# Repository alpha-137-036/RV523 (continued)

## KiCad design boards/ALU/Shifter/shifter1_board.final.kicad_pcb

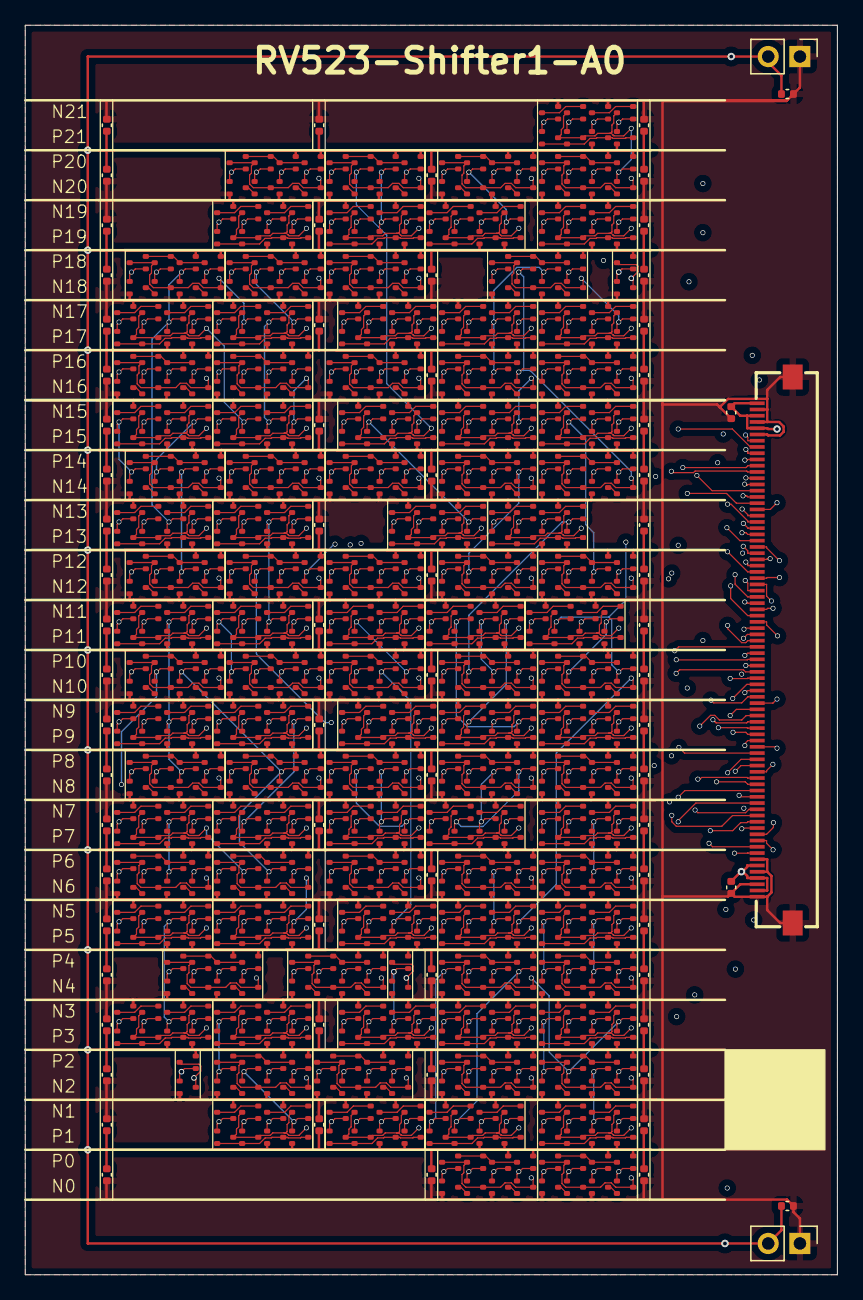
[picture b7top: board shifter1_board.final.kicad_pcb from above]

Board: 4 copper layers, 65.0 x 100.0 mm, 847 parts (0 on the bottom side), 426 nets.

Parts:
C1, C2, C3, C4: C_0402_1005Metric
j1: FPC-SMD_THD0518-80CL-GF
j2, j3: PinHeader_1x02_P2.54mm_Vertical
sh1._185_.N1, sh1._185_.N2, sh1._185_.N3, sh1._185_.N4, sh1._186_.N1, sh1._186_.N2, sh1._186_.N3, sh1._186_.N4, sh1._187_.N1, sh1._187_.N2, sh1._187_.N3, sh1._187_.N4, sh1._188_.N1, sh1._188_.N2, sh1._188_.N3, sh1._188_.N4, sh1._189_.N1, sh1._189_.N2, sh1._189_.N3, sh1._189_.N4, sh1._190_.N1, sh1._190_.N2, sh1._190_.N3, sh1._190_.N4, sh1._191_.N1, sh1._191_.N2, sh1._191_.N3, sh1._191_.N4, sh1._192_.N1, sh1._192_.N2, sh1._192_.N3, sh1._192_.N4, sh1._193_.N1, sh1._193_.N2, sh1._193_.N3, sh1._193_.N4, sh1._194_.N1, sh1._194_.N2, sh1._194_.N3, sh1._194_.N4, sh1._195_.N1, sh1._195_.N2, sh1._195_.N3, sh1._195_.N4, sh1._196_.N1, sh1._196_.N2, sh1._196_.N3, sh1._196_.N4, sh1._197_.N1, sh1._197_.N2, sh1._197_.N3, sh1._197_.N4, sh1._198_.N1, sh1._198_.N2, sh1._198_.N3, sh1._198_.N4, sh1._199_.N1, sh1._199_.N2, sh1._199_.N3, sh1._199_.N4, sh1._200_.N1, sh1._200_.N2, sh1._200_.N3, sh1._200_.N4, sh1._201_.N1, sh1._201_.N2, sh1._201_.N3, sh1._201_.N4, sh1._202_.N1, sh1._202_.N2, sh1._202_.N3, sh1._202_.N4, sh1._203_.N1, sh1._203_.N2, sh1._203_.N3, sh1._203_.N4, sh1._204_.N1, sh1._204_.N2, sh1._204_.N3, sh1._204_.N4, sh1._205_.N1, sh1._205_.N2, sh1._205_.N3, sh1._205_.N4, sh1._206_.N1, sh1._206_.N2, sh1._206_.N3, sh1._206_.N4, sh1._207_.N1, sh1._207_.N2, sh1._207_.N3, sh1._207_.N4, sh1._208_.N1, sh1._208_.N2, sh1._208_.N3, sh1._208_.N4, sh1._209_.N1, sh1._209_.N2, sh1._209_.N3, sh1._209_.N4, sh1._210_.N1, sh1._210_.N2, sh1._210_.N3, sh1._210_.N4, sh1._211_.N1, sh1._211_.N2, sh1._211_.N3, sh1._211_.N4, sh1._212_.N1, sh1._212_.N2, sh1._212_.N3, sh1._212_.N4, sh1._213_.N1, sh1._213_.N2, sh1._213_.N3, sh1._213_.N4, sh1._214_.N1, sh1._214_.N2, sh1._214_.N3, sh1._214_.N4, sh1._215_.N1, sh1._215_.N2, sh1._215_.N3, sh1._215_.N4, sh1._216_.N1, sh1._216_.N2, sh1._216_.N3, sh1._216_.N4, sh1._217_.N1, sh1._218_.N1, sh1._219_.N1, sh1._220_.N1, sh1._220_.N2, sh1._220_.N3, sh1._220_.N4, sh1._221_.N1, sh1._221_.N2, sh1._221_.N3, sh1._221_.N4, sh1._222_.N1, sh1._222_.N2, sh1._222_.N3, sh1._222_.N4, sh1._223_.N1, sh1._223_.N2, sh1._223_.N3, sh1._223_.N4, sh1._224_.N1, sh1._224_.N2, sh1._224_.N3, sh1._224_.N4, sh1._225_.N1, sh1._225_.N2, sh1._225_.N3, sh1._225_.N4, sh1._226_.N1, sh1._226_.N2, sh1._226_.N3, sh1._226_.N4, sh1._227_.N1, sh1._227_.N2, sh1._227_.N3, sh1._227_.N4, sh1._228_.N1, sh1._228_.N2, sh1._228_.N3, sh1._228_.N4, sh1._229_.N1, sh1._229_.N2, sh1._229_.N3, sh1._229_.N4, sh1._230_.N1, sh1._230_.N2, sh1._230_.N3, sh1._230_.N4, sh1._231_.N1, sh1._231_.N2, sh1._231_.N3, sh1._231_.N4, sh1._232_.N1, sh1._232_.N2, sh1._232_.N3, sh1._232_.N4, sh1._233_.N1, sh1._233_.N2, sh1._233_.N3, sh1._233_.N4, sh1._234_.N1, sh1._234_.N2, sh1._234_.N3, sh1._234_.N4, sh1._235_.N1, sh1._235_.N2, sh1._235_.N3, sh1._235_.N4, sh1._236_.N1, sh1._236_.N2, sh1._236_.N3, sh1._236_.N4, sh1._237_.N1, sh1._237_.N2, sh1._237_.N3, sh1._237_.N4, sh1._238_.N1, sh1._238_.N2, sh1._238_.N3, sh1._238_.N4, sh1._239_.N1, sh1._239_.N2, sh1._239_.N3, sh1._239_.N4, sh1._240_.N1, sh1._240_.N2, sh1._240_.N3, sh1._240_.N4, sh1._241_.N1, sh1._241_.N2, sh1._241_.N3, sh1._241_.N4, sh1._242_.N1, sh1._242_.N2, sh1._242_.N3, sh1._242_.N4, sh1._243_.N1, sh1._243_.N2, sh1._243_.N3, sh1._243_.N4, sh1._244_.N1, sh1._244_.N2, sh1._244_.N3, sh1._244_.N4, sh1._245_.N1, sh1._245_.N2, sh1._245_.N3, sh1._245_.N4, sh1._246_.N1, sh1._246_.N2, sh1._246_.N3, sh1._246_.N4, sh1._247_.N1, sh1._247_.N2, sh1._247_.N3, sh1._247_.N4, sh1._248_.N1, sh1._248_.N2, sh1._248_.N3, sh1._248_.N4, sh1._249_.N1, sh1._249_.N2, sh1._249_.N3, sh1._249_.N4, sh1._250_.N1, sh1._250_.N2, sh1._250_.N3, sh1._250_.N4, sh1._251_.N1, sh1._251_.N2, sh1._251_.N3, sh1._251_.N4, sh1._252_.N1, sh1._252_.N2, sh1._252_.N3, sh1._252_.N4, sh1._253_.N1, sh1._253_.N2, sh1._253_.N3, sh1._253_.N4, sh1._254_.N1, sh1._254_.N2, sh1._254_.N3, sh1._254_.N4, sh1._255_.N1, sh1._255_.N2, sh1._255_.N3, sh1._255_.N4, sh1._256_.N1, sh1._256_.N2, sh1._256_.N3, sh1._256_.N4, sh1._257_.N1, sh1._257_.N2, sh1._257_.N3, sh1._257_.N4, sh1._258_.N1, sh1._258_.N2, sh1._258_.N3, sh1._258_.N4, sh1._259_.N1, sh1._259_.N2, sh1._259_.N3, sh1._259_.N4, sh1._260_.N1, sh1._260_.N2, sh1._260_.N3, sh1._260_.N4, sh1._261_.N1, sh1._261_.N2, sh1._261_.N3, sh1._261_.N4, sh1._262_.N1, sh1._262_.N2, sh1._262_.N3, sh1._262_.N4, sh1._263_.N1, sh1._263_.N2, sh1._263_.N3, sh1._263_.N4, sh1._264_.N1, sh1._264_.N2, sh1._264_.N3, sh1._264_.N4, sh1._265_.N1, sh1._265_.N2, sh1._265_.N3, sh1._265_.N4, sh1._266_.N1, sh1._266_.N2, sh1._266_.N3, sh1._266_.N4, sh1._267_.N1, sh1._267_.N2, sh1._267_.N3, sh1._267_.N4, sh1._268_.N1, sh1._268_.N2, sh1._268_.N3, sh1._268_.N4, sh1._269_.N1, sh1._269_.N2, sh1._269_.N3, sh1._269_.N4, sh1._270_.N1, sh1._270_.N2, sh1._270_.N3, sh1._270_.N4, sh1._271_.N1, sh1._271_.N2, sh1._271_.N3, sh1._271_.N4, sh1._272_.N1, sh1._272_.N2, sh1._272_.N3, sh1._272_.N4, sh1._273_.N1, sh1._273_.N2, sh1._273_.N3, sh1._273_.N4, sh1._274_.N1, sh1._274_.N2, sh1._274_.N3, sh1._274_.N4, sh1._275_.N1, sh1._275_.N2, sh1._275_.N3, sh1._275_.N4, sh1._276_.N1, sh1._276_.N2, sh1._276_.N3, sh1._276_.N4, sh1._277_.N1, sh1._277_.N2, sh1._277_.N3, sh1._277_.N4, sh1._278_.N1, sh1._278_.N2, sh1._278_.N3, sh1._278_.N4, sh1._279_.N1, sh1._279_.N2, sh1._279_.N3, sh1._279_.N4, sh1._280_.N1, sh1._280_.N2, sh1._280_.N3, sh1._280_.N4, sh1._281_.N1, sh1._281_.N2, sh1._281_.N3, sh1._281_.N4, sh1._282_.N1, sh1._282_.N2, sh1._282_.N3, sh1._282_.N4, sh1._283_.N1, sh1._283_.N2, sh1._283_.N3, sh1._283_.N4: NMOS; SOT523
sh1._185_.P1, sh1._185_.P2, sh1._185_.P3, sh1._185_.P4, sh1._186_.P1, sh1._186_.P2, sh1._186_.P3, sh1._186_.P4, sh1._187_.P1, sh1._187_.P2, sh1._187_.P3, sh1._187_.P4, sh1._188_.P1, sh1._188_.P2, sh1._188_.P3, sh1._188_.P4, sh1._189_.P1, sh1._189_.P2, sh1._189_.P3, sh1._189_.P4, sh1._190_.P1, sh1._190_.P2, sh1._190_.P3, sh1._190_.P4, sh1._191_.P1, sh1._191_.P2, sh1._191_.P3, sh1._191_.P4, sh1._192_.P1, sh1._192_.P2, sh1._192_.P3, sh1._192_.P4, sh1._193_.P1, sh1._193_.P2, sh1._193_.P3, sh1._193_.P4, sh1._194_.P1, sh1._194_.P2, sh1._194_.P3, sh1._194_.P4, sh1._195_.P1, sh1._195_.P2, sh1._195_.P3, sh1._195_.P4, sh1._196_.P1, sh1._196_.P2, sh1._196_.P3, sh1._196_.P4, sh1._197_.P1, sh1._197_.P2, sh1._197_.P3, sh1._197_.P4, sh1._198_.P1, sh1._198_.P2, sh1._198_.P3, sh1._198_.P4, sh1._199_.P1, sh1._199_.P2, sh1._199_.P3, sh1._199_.P4, sh1._200_.P1, sh1._200_.P2, sh1._200_.P3, sh1._200_.P4, sh1._201_.P1, sh1._201_.P2, sh1._201_.P3, sh1._201_.P4, sh1._202_.P1, sh1._202_.P2, sh1._202_.P3, sh1._202_.P4, sh1._203_.P1, sh1._203_.P2, sh1._203_.P3, sh1._203_.P4, sh1._204_.P1, sh1._204_.P2, sh1._204_.P3, sh1._204_.P4, sh1._205_.P1, sh1._205_.P2, sh1._205_.P3, sh1._205_.P4, sh1._206_.P1, sh1._206_.P2, sh1._206_.P3, sh1._206_.P4, sh1._207_.P1, sh1._207_.P2, sh1._207_.P3, sh1._207_.P4, sh1._208_.P1, sh1._208_.P2, sh1._208_.P3, sh1._208_.P4, sh1._209_.P1, sh1._209_.P2, sh1._209_.P3, sh1._209_.P4, sh1._210_.P1, sh1._210_.P2, sh1._210_.P3, sh1._210_.P4, sh1._211_.P1, sh1._211_.P2, sh1._211_.P3, sh1._211_.P4, sh1._212_.P1, sh1._212_.P2, sh1._212_.P3, sh1._212_.P4, sh1._213_.P1, sh1._213_.P2, sh1._213_.P3, sh1._213_.P4, sh1._214_.P1, sh1._214_.P2, sh1._214_.P3, sh1._214_.P4, sh1._215_.P1, sh1._215_.P2, sh1._215_.P3, sh1._215_.P4, sh1._216_.P1, sh1._216_.P2, sh1._216_.P3, sh1._216_.P4, sh1._217_.P1, sh1._218_.P1, sh1._219_.P1, sh1._220_.P1, sh1._220_.P2, sh1._220_.P3, sh1._220_.P4, sh1._221_.P1, sh1._221_.P2, sh1._221_.P3, sh1._221_.P4, sh1._222_.P1, sh1._222_.P2, sh1._222_.P3, sh1._222_.P4, sh1._223_.P1, sh1._223_.P2, sh1._223_.P3, sh1._223_.P4, sh1._224_.P1, sh1._224_.P2, sh1._224_.P3, sh1._224_.P4, sh1._225_.P1, sh1._225_.P2, sh1._225_.P3, sh1._225_.P4, sh1._226_.P1, sh1._226_.P2, sh1._226_.P3, sh1._226_.P4, sh1._227_.P1, sh1._227_.P2, sh1._227_.P3, sh1._227_.P4, sh1._228_.P1, sh1._228_.P2, sh1._228_.P3, sh1._228_.P4, sh1._229_.P1, sh1._229_.P2, sh1._229_.P3, sh1._229_.P4, sh1._230_.P1, sh1._230_.P2, sh1._230_.P3, sh1._230_.P4, sh1._231_.P1, sh1._231_.P2, sh1._231_.P3, sh1._231_.P4, sh1._232_.P1, sh1._232_.P2, sh1._232_.P3, sh1._232_.P4, sh1._233_.P1, sh1._233_.P2, sh1._233_.P3, sh1._233_.P4, sh1._234_.P1, sh1._234_.P2, sh1._234_.P3, sh1._234_.P4, sh1._235_.P1, sh1._235_.P2, sh1._235_.P3, sh1._235_.P4, sh1._236_.P1, sh1._236_.P2, sh1._236_.P3, sh1._236_.P4, sh1._237_.P1, sh1._237_.P2, sh1._237_.P3, sh1._237_.P4, sh1._238_.P1, sh1._238_.P2, sh1._238_.P3, sh1._238_.P4, sh1._239_.P1, sh1._239_.P2, sh1._239_.P3, sh1._239_.P4, sh1._240_.P1, sh1._240_.P2, sh1._240_.P3, sh1._240_.P4, sh1._241_.P1, sh1._241_.P2, sh1._241_.P3, sh1._241_.P4, sh1._242_.P1, sh1._242_.P2, sh1._242_.P3, sh1._242_.P4, sh1._243_.P1, sh1._243_.P2, sh1._243_.P3, sh1._243_.P4, sh1._244_.P1, sh1._244_.P2, sh1._244_.P3, sh1._244_.P4, sh1._245_.P1, sh1._245_.P2, sh1._245_.P3, sh1._245_.P4, sh1._246_.P1, sh1._246_.P2, sh1._246_.P3, sh1._246_.P4, sh1._247_.P1, sh1._247_.P2, sh1._247_.P3, sh1._247_.P4, sh1._248_.P1, sh1._248_.P2, sh1._248_.P3, sh1._248_.P4, sh1._249_.P1, sh1._249_.P2, sh1._249_.P3, sh1._249_.P4, sh1._250_.P1, sh1._250_.P2, sh1._250_.P3, sh1._250_.P4, sh1._251_.P1, sh1._251_.P2, sh1._251_.P3, sh1._251_.P4, sh1._252_.P1, sh1._252_.P2, sh1._252_.P3, sh1._252_.P4, sh1._253_.P1, sh1._253_.P2, sh1._253_.P3, sh1._253_.P4, sh1._254_.P1, sh1._254_.P2, sh1._254_.P3, sh1._254_.P4, sh1._255_.P1, sh1._255_.P2, sh1._255_.P3, sh1._255_.P4, sh1._256_.P1, sh1._256_.P2, sh1._256_.P3, sh1._256_.P4, sh1._257_.P1, sh1._257_.P2, sh1._257_.P3, sh1._257_.P4, sh1._258_.P1, sh1._258_.P2, sh1._258_.P3, sh1._258_.P4, sh1._259_.P1, sh1._259_.P2, sh1._259_.P3, sh1._259_.P4, sh1._260_.P1, sh1._260_.P2, sh1._260_.P3, sh1._260_.P4, sh1._261_.P1, sh1._261_.P2, sh1._261_.P3, sh1._261_.P4, sh1._262_.P1, sh1._262_.P2, sh1._262_.P3, sh1._262_.P4, sh1._263_.P1, sh1._263_.P2, sh1._263_.P3, sh1._263_.P4, sh1._264_.P1, sh1._264_.P2, sh1._264_.P3, sh1._264_.P4, sh1._265_.P1, sh1._265_.P2, sh1._265_.P3, sh1._265_.P4, sh1._266_.P1, sh1._266_.P2, sh1._266_.P3, sh1._266_.P4, sh1._267_.P1, sh1._267_.P2, sh1._267_.P3, sh1._267_.P4, sh1._268_.P1, sh1._268_.P2, sh1._268_.P3, sh1._268_.P4, sh1._269_.P1, sh1._269_.P2, sh1._269_.P3, sh1._269_.P4, sh1._270_.P1, sh1._270_.P2, sh1._270_.P3, sh1._270_.P4, sh1._271_.P1, sh1._271_.P2, sh1._271_.P3, sh1._271_.P4, sh1._272_.P1, sh1._272_.P2, sh1._272_.P3, sh1._272_.P4, sh1._273_.P1, sh1._273_.P2, sh1._273_.P3, sh1._273_.P4, sh1._274_.P1, sh1._274_.P2, sh1._274_.P3, sh1._274_.P4, sh1._275_.P1, sh1._275_.P2, sh1._275_.P3, sh1._275_.P4, sh1._276_.P1, sh1._276_.P2, sh1._276_.P3, sh1._276_.P4, sh1._277_.P1, sh1._277_.P2, sh1._277_.P3, sh1._277_.P4, sh1._278_.P1, sh1._278_.P2, sh1._278_.P3, sh1._278_.P4, sh1._279_.P1, sh1._279_.P2, sh1._279_.P3, sh1._279_.P4, sh1._280_.P1, sh1._280_.P2, sh1._280_.P3, sh1._280_.P4, sh1._281_.P1, sh1._281_.P2, sh1._281_.P3, sh1._281_.P4, sh1._282_.P1, sh1._282_.P2, sh1._282_.P3, sh1._282_.P4, sh1._283_.P1, sh1._283_.P2, sh1._283_.P3, sh1._283_.P4: PMOS; SOT523
sh1.decap0_L.C, sh1.decap0_M.C, sh1.decap0_R.C, sh1.decap1_L.C, sh1.decap1_M.C, sh1.decap1_R.C, sh1.decap2_L.C, sh1.decap2_M.C, sh1.decap2_R.C, sh1.decap3_L.C, sh1.decap3_M.C, sh1.decap3_R.C, sh1.decap4_L.C, sh1.decap4_M.C, sh1.decap4_R.C, sh1.decap5_L.C, sh1.decap5_M.C, sh1.decap5_R.C, sh1.decap6_L.C, sh1.decap6_M.C, sh1.decap6_R.C, sh1.decap7_L.C, sh1.decap7_M.C, sh1.decap7_R.C, sh1.decap8_L.C, sh1.decap8_M.C, sh1.decap8_R.C, sh1.decap9_L.C, sh1.decap9_M.C, sh1.decap9_R.C, sh1.decap10_L.C, sh1.decap10_M.C, sh1.decap10_R.C, sh1.decap11_L.C, sh1.decap11_M.C, sh1.decap11_R.C, sh1.decap12_L.C, sh1.decap12_M.C, sh1.decap12_R.C, sh1.decap13_L.C, sh1.decap13_M.C, sh1.decap13_R.C, sh1.decap14_L.C, sh1.decap14_M.C, sh1.decap14_R.C, sh1.decap15_L.C, sh1.decap15_M.C, sh1.decap15_R.C, sh1.decap16_L.C, sh1.decap16_M.C, sh1.decap16_R.C, sh1.decap17_L.C, sh1.decap17_M.C, sh1.decap17_R.C, sh1.decap18_L.C, sh1.decap18_M.C, sh1.decap18_R.C, sh1.decap19_L.C, sh1.decap19_M.C, sh1.decap19_R.C, sh1.decap20_L.C, sh1.decap20_M.C, sh1.decap20_R.C, sh1.decap21_L.C, sh1.decap21_M.C, sh1.decap21_R.C: 0.1u; C_0402_1005Metric

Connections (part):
A0: j1.74 (pins.74), sh1._219_.N1.1 (G), sh1._219_.P1.1 (G), sh1._252_.N4.1 (G), sh1._252_.P4.1 (G), sh1._263_.N4.1 (G), sh1._263_.P4.1 (G)
A.0: j1.71 (pins.71), sh1._193_.N3.1 (G), sh1._193_.P3.1 (G), sh1._200_.N2.1 (G), sh1._200_.P2.1 (G)
A.1: j1.69 (pins.69), sh1._192_.N4.1 (G), sh1._192_.P4.1 (G), sh1._211_.N2.1 (G), sh1._211_.P2.1 (G)
A.2: j1.67 (pins.67), sh1._190_.N2.1 (G), sh1._190_.P2.1 (G), sh1._191_.N4.1 (G), sh1._191_.P4.1 (G)
A.3: j1.65 (pins.65), sh1._189_.N4.1 (G), sh1._189_.P4.1 (G), sh1._194_.N2.1 (G), sh1._194_.P2.1 (G)
A.4: j1.63 (pins.63), sh1._188_.N4.1 (G), sh1._188_.P4.1 (G), sh1._195_.N2.1 (G), sh1._195_.P2.1 (G)
A.5: j1.61 (pins.61), sh1._187_.N4.1 (G), sh1._187_.P4.1 (G), sh1._196_.N2.1 (G), sh1._196_.P2.1 (G)
A.6: j1.59 (pins.59), sh1._186_.N4.1 (G), sh1._186_.P4.1 (G), sh1._197_.N2.1 (G), sh1._197_.P2.1 (G)
A.7: j1.57 (pins.57), sh1._185_.N4.1 (G), sh1._185_.P4.1 (G), sh1._198_.N2.1 (G), sh1._198_.P2.1 (G)
A.8: j1.55 (pins.55), sh1._199_.N2.1 (G), sh1._199_.P2.1 (G), sh1._216_.N4.1 (G), sh1._216_.P4.1 (G)
A.9: j1.53 (pins.53), sh1._201_.N2.1 (G), sh1._201_.P2.1 (G), sh1._215_.N4.1 (G), sh1._215_.P4.1 (G)
A.10: j1.51 (pins.51), sh1._202_.N2.1 (G), sh1._202_.P2.1 (G), sh1._214_.N4.1 (G), sh1._214_.P4.1 (G)
A.11: j1.49 (pins.49), sh1._203_.N2.1 (G), sh1._203_.P2.1 (G), sh1._213_.N4.1 (G), sh1._213_.P4.1 (G)
A.12: j1.47 (pins.47), sh1._204_.N2.1 (G), sh1._204_.P2.1 (G), sh1._212_.N4.1 (G), sh1._212_.P4.1 (G)
A.13: j1.45 (pins.45), sh1._205_.N2.1 (G), sh1._205_.P2.1 (G), sh1._210_.N4.1 (G), sh1._210_.P4.1 (G)
A.14: j1.43 (pins.43), sh1._206_.N2.1 (G), sh1._206_.P2.1 (G), sh1._209_.N4.1 (G), sh1._209_.P4.1 (G)
A.15: j1.41 (pins.41), sh1._207_.N2.1 (G), sh1._207_.P2.1 (G), sh1._208_.N4.1 (G), sh1._208_.P4.1 (G)
A.16: j1.39 (pins.39), sh1._207_.N4.1 (G), sh1._207_.P4.1 (G), sh1._208_.N2.1 (G), sh1._208_.P2.1 (G)
A.17: j1.37 (pins.37), sh1._206_.N4.1 (G), sh1._206_.P4.1 (G), sh1._209_.N2.1 (G), sh1._209_.P2.1 (G)
A.18: j1.35 (pins.35), sh1._205_.N4.1 (G), sh1._205_.P4.1 (G), sh1._210_.N2.1 (G), sh1._210_.P2.1 (G)
A.19: j1.33 (pins.33), sh1._204_.N4.1 (G), sh1._204_.P4.1 (G), sh1._212_.N2.1 (G), sh1._212_.P2.1 (G)
A.20: j1.31 (pins.31), sh1._203_.N4.1 (G), sh1._203_.P4.1 (G), sh1._213_.N2.1 (G), sh1._213_.P2.1 (G)
A.21: j1.29 (pins.29), sh1._202_.N4.1 (G), sh1._202_.P4.1 (G), sh1._214_.N2.1 (G), sh1._214_.P2.1 (G)
A.22: j1.27 (pins.27), sh1._201_.N4.1 (G), sh1._201_.P4.1 (G), sh1._215_.N2.1 (G), sh1._215_.P2.1 (G)
A.23: j1.25 (pins.25), sh1._199_.N4.1 (G), sh1._199_.P4.1 (G), sh1._216_.N2.1 (G), sh1._216_.P2.1 (G)
A.24: j1.23 (pins.23), sh1._185_.N2.1 (G), sh1._185_.P2.1 (G), sh1._198_.N4.1 (G), sh1._198_.P4.1 (G)
A.25: j1.21 (pins.21), sh1._186_.N2.1 (G), sh1._186_.P2.1 (G), sh1._197_.N4.1 (G), sh1._197_.P4.1 (G)
A.26: j1.19 (pins.19), sh1._187_.N2.1 (G), sh1._187_.P2.1 (G), sh1._196_.N4.1 (G), sh1._196_.P4.1 (G)
A.27: j1.17 (pins.17), sh1._188_.N2.1 (G), sh1._188_.P2.1 (G), sh1._195_.N4.1 (G), sh1._195_.P4.1 (G)
A.28: j1.15 (pins.15), sh1._189_.N2.1 (G), sh1._189_.P2.1 (G), sh1._194_.N4.1 (G), sh1._194_.P4.1 (G)
A.29: j1.13 (pins.13), sh1._190_.N4.1 (G), sh1._190_.P4.1 (G), sh1._191_.N2.1 (G), sh1._191_.P2.1 (G)
A.30: j1.11 (pins.11), sh1._192_.N2.1 (G), sh1._192_.P2.1 (G), sh1._211_.N4.1 (G), sh1._211_.P4.1 (G)
A.31: j1.9 (pins.9), sh1._193_.N2.1 (G), sh1._193_.P2.1 (G), sh1._200_.N4.1 (G), sh1._200_.P4.1 (G)
B.0: sh1._217_.N1.1 (G), sh1._217_.P1.1 (G), sh1._220_.N3.1 (G), sh1._220_.P3.1 (G), sh1._221_.N3.1 (G), sh1._221_.P3.1 (G), sh1._222_.N3.1 (G), sh1._222_.P3.1 (G), sh1._223_.N3.1 (G), sh1._223_.P3.1 (G), sh1._224_.N3.1 (G), sh1._224_.P3.1 (G), sh1._225_.N3.1 (G), sh1._225_.P3.1 (G), sh1._226_.N3.1 (G), sh1._226_.P3.1 (G), sh1._227_.N3.1 (G), sh1._227_.P3.1 (G), sh1._228_.N3.1 (G), sh1._228_.P3.1 (G), sh1._229_.N3.1 (G), sh1._229_.P3.1 (G), sh1._230_.N3.1 (G), sh1._230_.P3.1 (G), sh1._231_.N3.1 (G), sh1._231_.P3.1 (G), sh1._232_.N3.1 (G), sh1._232_.P3.1 (G), sh1._233_.N3.1 (G), sh1._233_.P3.1 (G), sh1._234_.N3.1 (G), sh1._234_.P3.1 (G), sh1._235_.N3.1 (G), sh1._235_.P3.1 (G), sh1._236_.N3.1 (G), sh1._236_.P3.1 (G), sh1._237_.N3.1 (G), sh1._237_.P3.1 (G), sh1._238_.N3.1 (G), sh1._238_.P3.1 (G), sh1._239_.N3.1 (G), sh1._239_.P3.1 (G), sh1._240_.N3.1 (G), sh1._240_.P3.1 (G), sh1._241_.N3.1 (G), sh1._241_.P3.1 (G), sh1._242_.N3.1 (G), sh1._242_.P3.1 (G), sh1._243_.N3.1 (G), sh1._243_.P3.1 (G), sh1._244_.N3.1 (G), sh1._244_.P3.1 (G), sh1._245_.N3.1 (G), sh1._245_.P3.1 (G), sh1._246_.N3.1 (G), sh1._246_.P3.1 (G), sh1._247_.N3.1 (G), sh1._247_.P3.1 (G), sh1._248_.N3.1 (G), sh1._248_.P3.1 (G), sh1._249_.N3.1 (G), sh1._249_.P3.1 (G), sh1._250_.N3.1 (G), sh1._250_.P3.1 (G), sh1._251_.N3.1 (G), sh1._251_.P3.1 (G)
B.1: sh1._218_.N1.1 (G), sh1._218_.P1.1 (G), sh1._252_.N3.1 (G), sh1._252_.P3.1 (G), sh1._253_.N3.1 (G), sh1._253_.P3.1 (G), sh1._254_.N3.1 (G), sh1._254_.P3.1 (G), sh1._255_.N3.1 (G), sh1._255_.P3.1 (G), sh1._256_.N3.1 (G), sh1._256_.P3.1 (G), sh1._257_.N3.1 (G), sh1._257_.P3.1 (G), sh1._258_.N3.1 (G), sh1._258_.P3.1 (G), sh1._259_.N3.1 (G), sh1._259_.P3.1 (G), sh1._260_.N3.1 (G), sh1._260_.P3.1 (G), sh1._261_.N3.1 (G), sh1._261_.P3.1 (G), sh1._262_.N3.1 (G), sh1._262_.P3.1 (G), sh1._263_.N3.1 (G), sh1._263_.P3.1 (G), sh1._264_.N3.1 (G), sh1._264_.P3.1 (G), sh1._265_.N3.1 (G), sh1._265_.P3.1 (G), sh1._266_.N3.1 (G), sh1._266_.P3.1 (G), sh1._267_.N3.1 (G), sh1._267_.P3.1 (G), sh1._268_.N3.1 (G), sh1._268_.P3.1 (G), sh1._269_.N3.1 (G), sh1._269_.P3.1 (G), sh1._270_.N3.1 (G), sh1._270_.P3.1 (G), sh1._271_.N3.1 (G), sh1._271_.P3.1 (G), sh1._272_.N3.1 (G), sh1._272_.P3.1 (G), sh1._273_.N3.1 (G), sh1._273_.P3.1 (G), sh1._274_.N3.1 (G), sh1._274_.P3.1 (G), sh1._275_.N3.1 (G), sh1._275_.P3.1 (G), sh1._276_.N3.1 (G), sh1._276_.P3.1 (G), sh1._277_.N3.1 (G), sh1._277_.P3.1 (G), sh1._278_.N3.1 (G), sh1._278_.P3.1 (G), sh1._279_.N3.1 (G), sh1._279_.P3.1 (G), sh1._280_.N3.1 (G), sh1._280_.P3.1 (G), sh1._281_.N3.1 (G), sh1._281_.P3.1 (G), sh1._282_.N3.1 (G), sh1._282_.P3.1 (G), sh1._283_.N3.1 (G), sh1._283_.P3.1 (G)
F.0: j1.70 (pins.70), sh1._252_.N2.3 (D), sh1._252_.N4.3 (D), sh1._252_.P1.3 (D), sh1._252_.P2.3 (D)
F.1: j1.68 (pins.68), sh1._263_.N2.3 (D), sh1._263_.N4.3 (D), sh1._263_.P1.3 (D), sh1._263_.P2.3 (D)
F.2: j1.66 (pins.66), sh1._274_.N2.3 (D), sh1._274_.N4.3 (D), sh1._274_.P1.3 (D), sh1._274_.P2.3 (D)
F.3: j1.64 (pins.64), sh1._277_.N2.3 (D), sh1._277_.N4.3 (D), sh1._277_.P1.3 (D), sh1._277_.P2.3 (D)
F.4: j1.62 (pins.62), sh1._278_.N2.3 (D), sh1._278_.N4.3 (D), sh1._278_.P1.3 (D), sh1._278_.P2.3 (D)
F.5: j1.60 (pins.60), sh1._279_.N2.3 (D), sh1._279_.N4.3 (D), sh1._279_.P1.3 (D), sh1._279_.P2.3 (D)
F.6: j1.58 (pins.58), sh1._280_.N2.3 (D), sh1._280_.N4.3 (D), sh1._280_.P1.3 (D), sh1._280_.P2.3 (D)
F.7: j1.56 (pins.56), sh1._281_.N2.3 (D), sh1._281_.N4.3 (D), sh1._281_.P1.3 (D), sh1._281_.P2.3 (D)
F.8: j1.54 (pins.54), sh1._282_.N2.3 (D), sh1._282_.N4.3 (D), sh1._282_.P1.3 (D), sh1._282_.P2.3 (D)
F.9: j1.52 (pins.52), sh1._283_.N2.3 (D), sh1._283_.N4.3 (D), sh1._283_.P1.3 (D), sh1._283_.P2.3 (D)
F.10: j1.50 (pins.50), sh1._253_.N2.3 (D), sh1._253_.N4.3 (D), sh1._253_.P1.3 (D), sh1._253_.P2.3 (D)
F.11: j1.48 (pins.48), sh1._254_.N2.3 (D), sh1._254_.N4.3 (D), sh1._254_.P1.3 (D), sh1._254_.P2.3 (D)
F.12: j1.46 (pins.46), sh1._255_.N2.3 (D), sh1._255_.N4.3 (D), sh1._255_.P1.3 (D), sh1._255_.P2.3 (D)
F.13: j1.44 (pins.44), sh1._256_.N2.3 (D), sh1._256_.N4.3 (D), sh1._256_.P1.3 (D), sh1._256_.P2.3 (D)
F.14: j1.42 (pins.42), sh1._257_.N2.3 (D), sh1._257_.N4.3 (D), sh1._257_.P1.3 (D), sh1._257_.P2.3 (D)
F.15: j1.40 (pins.40), sh1._258_.N2.3 (D), sh1._258_.N4.3 (D), sh1._258_.P1.3 (D), sh1._258_.P2.3 (D)
F.16: j1.38 (pins.38), sh1._259_.N2.3 (D), sh1._259_.N4.3 (D), sh1._259_.P1.3 (D), sh1._259_.P2.3 (D)
F.17: j1.36 (pins.36), sh1._260_.N2.3 (D), sh1._260_.N4.3 (D), sh1._260_.P1.3 (D), sh1._260_.P2.3 (D)
F.18: j1.34 (pins.34), sh1._261_.N2.3 (D), sh1._261_.N4.3 (D), sh1._261_.P1.3 (D), sh1._261_.P2.3 (D)
F.19: j1.32 (pins.32), sh1._262_.N2.3 (D), sh1._262_.N4.3 (D), sh1._262_.P1.3 (D), sh1._262_.P2.3 (D)
F.20: j1.30 (pins.30), sh1._264_.N2.3 (D), sh1._264_.N4.3 (D), sh1._264_.P1.3 (D), sh1._264_.P2.3 (D)
F.21: j1.28 (pins.28), sh1._265_.N2.3 (D), sh1._265_.N4.3 (D), sh1._265_.P1.3 (D), sh1._265_.P2.3 (D)
F.22: j1.26 (pins.26), sh1._266_.N2.3 (D), sh1._266_.N4.3 (D), sh1._266_.P1.3 (D), sh1._266_.P2.3 (D)
F.23: j1.24 (pins.24), sh1._267_.N2.3 (D), sh1._267_.N4.3 (D), sh1._267_.P1.3 (D), sh1._267_.P2.3 (D)
F.24: j1.22 (pins.22), sh1._268_.N2.3 (D), sh1._268_.N4.3 (D), sh1._268_.P1.3 (D), sh1._268_.P2.3 (D)
F.25: j1.20 (pins.20), sh1._269_.N2.3 (D), sh1._269_.N4.3 (D), sh1._269_.P1.3 (D), sh1._269_.P2.3 (D)
F.26: j1.18 (pins.18), sh1._270_.N2.3 (D), sh1._270_.N4.3 (D), sh1._270_.P1.3 (D), sh1._270_.P2.3 (D)
F.27: j1.16 (pins.16), sh1._271_.N2.3 (D), sh1._271_.N4.3 (D), sh1._271_.P1.3 (D), sh1._271_.P2.3 (D)
F.28: j1.14 (pins.14), sh1._272_.N2.3 (D), sh1._272_.N4.3 (D), sh1._272_.P1.3 (D), sh1._272_.P2.3 (D)
F.29: j1.12 (pins.12), sh1._273_.N2.3 (D), sh1._273_.N4.3 (D), sh1._273_.P1.3 (D), sh1._273_.P2.3 (D)
F.30: j1.10 (pins.10), sh1._275_.N2.3 (D), sh1._275_.N4.3 (D), sh1._275_.P1.3 (D), sh1._275_.P2.3 (D)
F.31: j1.8 (pins.8), sh1._276_.N2.3 (D), sh1._276_.N4.3 (D), sh1._276_.P1.3 (D), sh1._276_.P2.3 (D)
GND: C1.1, C2.1, C3.1, C4.1, j1.1 (pins.1), j1.3 (pins.3), j1.5 (pins.5), j1.7 (pins.7), j1.75 (pins.75), j1.77 (pins.77), j1.79 (pins.79), j1.81 (pins.81), j1.82 (pins.82), j2.1 (pins.1), j3.1 (pins.1), sh1._185_.N1.2 (S), sh1._185_.N3.2 (S), sh1._186_.N1.2 (S), sh1._186_.N3.2 (S), sh1._187_.N1.2 (S), sh1._187_.N3.2 (S), sh1._188_.N1.2 (S), sh1._188_.N3.2 (S), sh1._189_.N1.2 (S), sh1._189_.N3.2 (S), sh1._190_.N1.2 (S), sh1._190_.N3.2 (S), sh1._191_.N1.2 (S), sh1._191_.N3.2 (S), sh1._192_.N1.2 (S), sh1._192_.N3.2 (S), sh1._193_.N1.2 (S), sh1._193_.N3.2 (S), sh1._194_.N1.2 (S), sh1._194_.N3.2 (S), sh1._195_.N1.2 (S), sh1._195_.N3.2 (S), sh1._196_.N1.2 (S), sh1._196_.N3.2 (S), sh1._197_.N1.2 (S), sh1._197_.N3.2 (S), sh1._198_.N1.2 (S), sh1._198_.N3.2 (S), sh1._199_.N1.2 (S), sh1._199_.N3.2 (S), sh1._200_.N1.2 (S), sh1._200_.N3.2 (S), sh1._201_.N1.2 (S), sh1._201_.N3.2 (S), sh1._202_.N1.2 (S), sh1._202_.N3.2 (S), sh1._203_.N1.2 (S), sh1._203_.N3.2 (S), sh1._204_.N1.2 (S), sh1._204_.N3.2 (S), sh1._205_.N1.2 (S), sh1._205_.N3.2 (S), sh1._206_.N1.2 (S), sh1._206_.N3.2 (S), sh1._207_.N1.2 (S), sh1._207_.N3.2 (S), sh1._208_.N1.2 (S), sh1._208_.N3.2 (S), sh1._209_.N1.2 (S), sh1._209_.N3.2 (S), sh1._210_.N1.2 (S), sh1._210_.N3.2 (S), sh1._211_.N1.2 (S), sh1._211_.N3.2 (S), sh1._212_.N1.2 (S), sh1._212_.N3.2 (S), sh1._213_.N1.2 (S), sh1._213_.N3.2 (S), sh1._214_.N1.2 (S), sh1._214_.N3.2 (S), sh1._215_.N1.2 (S), sh1._215_.N3.2 (S), sh1._216_.N1.2 (S), sh1._216_.N3.2 (S), sh1._217_.N1.2 (S)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
VDD: C1.2, C2.2, C3.2, C4.2, j1.2 (pins.2), j1.4 (pins.4), j1.6 (pins.6), j1.76 (pins.76), j1.78 (pins.78), j1.80 (pins.80), j2.2 (pins.2), j3.2 (pins.2), sh1._185_.P3.2 (S), sh1._185_.P4.2 (S), sh1._186_.P3.2 (S), sh1._186_.P4.2 (S), sh1._187_.P3.2 (S), sh1._187_.P4.2 (S), sh1._188_.P3.2 (S), sh1._188_.P4.2 (S), sh1._189_.P3.2 (S), sh1._189_.P4.2 (S), sh1._190_.P3.2 (S), sh1._190_.P4.2 (S), sh1._191_.P3.2 (S), sh1._191_.P4.2 (S), sh1._192_.P3.2 (S), sh1._192_.P4.2 (S), sh1._193_.P3.2 (S), sh1._193_.P4.2 (S), sh1._194_.P3.2 (S), sh1._194_.P4.2 (S), sh1._195_.P3.2 (S), sh1._195_.P4.2 (S), sh1._196_.P3.2 (S), sh1._196_.P4.2 (S), sh1._197_.P3.2 (S), sh1._197_.P4.2 (S), sh1._198_.P3.2 (S), sh1._198_.P4.2 (S), sh1._199_.P3.2 (S), sh1._199_.P4.2 (S), sh1._200_.P3.2 (S), sh1._200_.P4.2 (S), sh1._201_.P3.2 (S), sh1._201_.P4.2 (S), sh1._202_.P3.2 (S), sh1._202_.P4.2 (S), sh1._203_.P3.2 (S), sh1._203_.P4.2 (S), sh1._204_.P3.2 (S), sh1._204_.P4.2 (S), sh1._205_.P3.2 (S), sh1._205_.P4.2 (S), sh1._206_.P3.2 (S), sh1._206_.P4.2 (S), sh1._207_.P3.2 (S), sh1._207_.P4.2 (S), sh1._208_.P3.2 (S), sh1._208_.P4.2 (S), sh1._209_.P3.2 (S), sh1._209_.P4.2 (S), sh1._210_.P3.2 (S), sh1._210_.P4.2 (S), sh1._211_.P3.2 (S), sh1._211_.P4.2 (S), sh1._212_.P3.2 (S), sh1._212_.P4.2 (S), sh1._213_.P3.2 (S), sh1._213_.P4.2 (S), sh1._214_.P3.2 (S), sh1._214_.P4.2 (S), sh1._215_.P3.2 (S), sh1._215_.P4.2 (S), sh1._216_.P3.2 (S), sh1._216_.P4.2 (S), sh1._217_.P1.2 (S), sh1._218_.P1.2 (S), sh1._219_.P1.2 (S), sh1._220_.P3.2 (S)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
pins.71: j1.72 (pins.72), sh1._185_.N1.1 (G), sh1._185_.P1.1 (G), sh1._186_.N1.1 (G), sh1._186_.P1.1 (G), sh1._187_.N1.1 (G), sh1._187_.P1.1 (G), sh1._188_.N1.1 (G), sh1._188_.P1.1 (G), sh1._189_.N1.1 (G), sh1._189_.P1.1 (G), sh1._190_.N1.1 (G), sh1._190_.P1.1 (G), sh1._191_.N1.1 (G), sh1._191_.P1.1 (G), sh1._192_.N1.1 (G), sh1._192_.P1.1 (G), sh1._193_.N1.1 (G), sh1._193_.P1.1 (G), sh1._194_.N1.1 (G), sh1._194_.P1.1 (G), sh1._195_.N1.1 (G), sh1._195_.P1.1 (G), sh1._196_.N1.1 (G), sh1._196_.P1.1 (G), sh1._197_.N1.1 (G), sh1._197_.P1.1 (G), sh1._198_.N1.1 (G), sh1._198_.P1.1 (G), sh1._199_.N1.1 (G), sh1._199_.P1.1 (G), sh1._200_.N1.1 (G), sh1._200_.P1.1 (G), sh1._201_.N1.1 (G), sh1._201_.P1.1 (G), sh1._202_.N1.1 (G), sh1._202_.P1.1 (G), sh1._203_.N1.1 (G), sh1._203_.P1.1 (G), sh1._204_.N1.1 (G), sh1._204_.P1.1 (G), sh1._205_.N1.1 (G), sh1._205_.P1.1 (G), sh1._206_.N1.1 (G), sh1._206_.P1.1 (G), sh1._207_.N1.1 (G), sh1._207_.P1.1 (G), sh1._208_.N1.1 (G), sh1._208_.P1.1 (G), sh1._209_.N1.1 (G), sh1._209_.P1.1 (G), sh1._210_.N1.1 (G), sh1._210_.P1.1 (G), sh1._211_.N1.1 (G), sh1._211_.P1.1 (G), sh1._212_.N1.1 (G), sh1._212_.P1.1 (G), sh1._213_.N1.1 (G), sh1._213_.P1.1 (G), sh1._214_.N1.1 (G), sh1._214_.P1.1 (G), sh1._215_.N1.1 (G), sh1._215_.P1.1 (G), sh1._216_.N1.1 (G), sh1._216_.P1.1 (G)
pins.72: j1.73 (pins.73), sh1._185_.N3.1 (G), sh1._185_.P3.1 (G), sh1._186_.N3.1 (G), sh1._186_.P3.1 (G), sh1._187_.N3.1 (G), sh1._187_.P3.1 (G), sh1._188_.N3.1 (G), sh1._188_.P3.1 (G), sh1._189_.N3.1 (G), sh1._189_.P3.1 (G), sh1._190_.N3.1 (G), sh1._190_.P3.1 (G), sh1._191_.N3.1 (G), sh1._191_.P3.1 (G), sh1._192_.N3.1 (G), sh1._192_.P3.1 (G), sh1._193_.N4.1 (G), sh1._193_.P4.1 (G), sh1._194_.N3.1 (G), sh1._194_.P3.1 (G), sh1._195_.N3.1 (G), sh1._195_.P3.1 (G), sh1._196_.N3.1 (G), sh1._196_.P3.1 (G), sh1._197_.N3.1 (G), sh1._197_.P3.1 (G), sh1._198_.N3.1 (G), sh1._198_.P3.1 (G), sh1._199_.N3.1 (G), sh1._199_.P3.1 (G), sh1._200_.N3.1 (G), sh1._200_.P3.1 (G), sh1._201_.N3.1 (G), sh1._201_.P3.1 (G), sh1._202_.N3.1 (G), sh1._202_.P3.1 (G), sh1._203_.N3.1 (G), sh1._203_.P3.1 (G), sh1._204_.N3.1 (G), sh1._204_.P3.1 (G), sh1._205_.N3.1 (G), sh1._205_.P3.1 (G), sh1._206_.N3.1 (G), sh1._206_.P3.1 (G), sh1._207_.N3.1 (G), sh1._207_.P3.1 (G), sh1._208_.N3.1 (G), sh1._208_.P3.1 (G), sh1._209_.N3.1 (G), sh1._209_.P3.1 (G), sh1._210_.N3.1 (G), sh1._210_.P3.1 (G), sh1._211_.N3.1 (G), sh1._211_.P3.1 (G), sh1._212_.N3.1 (G), sh1._212_.P3.1 (G), sh1._213_.N3.1 (G), sh1._213_.P3.1 (G), sh1._214_.N3.1 (G), sh1._214_.P3.1 (G), sh1._215_.N3.1 (G), sh1._215_.P3.1 (G), sh1._216_.N3.1 (G), sh1._216_.P3.1 (G)
sh1._035_: sh1._200_.N2.3 (D), sh1._200_.N4.3 (D), sh1._200_.P1.3 (D), sh1._200_.P2.3 (D), sh1._220_.N2.1 (G), sh1._220_.P2.1 (G), sh1._231_.N4.1 (G), sh1._231_.P4.1 (G)
sh1._036_: sh1._202_.N2.3 (D), sh1._202_.N4.3 (D), sh1._202_.P1.3 (D), sh1._202_.P2.3 (D), sh1._221_.N2.1 (G), sh1._221_.P2.1 (G), sh1._222_.N4.1 (G), sh1._222_.P4.1 (G)
sh1._037_: sh1._203_.N2.3 (D), sh1._203_.N4.3 (D), sh1._203_.P1.3 (D), sh1._203_.P2.3 (D), sh1._222_.N2.1 (G), sh1._222_.P2.1 (G), sh1._223_.N4.1 (G), sh1._223_.P4.1 (G)
sh1._038_: sh1._204_.N2.3 (D), sh1._204_.N4.3 (D), sh1._204_.P1.3 (D), sh1._204_.P2.3 (D), sh1._223_.N2.1 (G), sh1._223_.P2.1 (G), sh1._224_.N4.1 (G), sh1._224_.P4.1 (G)
sh1._039_: sh1._205_.N2.3 (D), sh1._205_.N4.3 (D), sh1._205_.P1.3 (D), sh1._205_.P2.3 (D), sh1._224_.N2.1 (G), sh1._224_.P2.1 (G), sh1._225_.N4.1 (G), sh1._225_.P4.1 (G)
sh1._040_: sh1._206_.N2.3 (D), sh1._206_.N4.3 (D), sh1._206_.P1.3 (D), sh1._206_.P2.3 (D), sh1._225_.N2.1 (G), sh1._225_.P2.1 (G), sh1._226_.N4.1 (G), sh1._226_.P4.1 (G)
sh1._041_: sh1._207_.N2.3 (D), sh1._207_.N4.3 (D), sh1._207_.P1.3 (D), sh1._207_.P2.3 (D), sh1._226_.N2.1 (G), sh1._226_.P2.1 (G), sh1._227_.N4.1 (G), sh1._227_.P4.1 (G)
sh1._042_: sh1._208_.N2.3 (D), sh1._208_.N4.3 (D), sh1._208_.P1.3 (D), sh1._208_.P2.3 (D), sh1._227_.N2.1 (G), sh1._227_.P2.1 (G), sh1._228_.N4.1 (G), sh1._228_.P4.1 (G)
sh1._043_: sh1._209_.N2.3 (D), sh1._209_.N4.3 (D), sh1._209_.P1.3 (D), sh1._209_.P2.3 (D), sh1._228_.N2.1 (G), sh1._228_.P2.1 (G), sh1._229_.N4.1 (G), sh1._229_.P4.1 (G)
sh1._044_: sh1._210_.N2.3 (D), sh1._210_.N4.3 (D), sh1._210_.P1.3 (D), sh1._210_.P2.3 (D), sh1._229_.N2.1 (G), sh1._229_.P2.1 (G), sh1._230_.N4.1 (G), sh1._230_.P4.1 (G)
sh1._045_: sh1._212_.N2.3 (D), sh1._212_.N4.3 (D), sh1._212_.P1.3 (D), sh1._212_.P2.3 (D), sh1._230_.N2.1 (G), sh1._230_.P2.1 (G), sh1._232_.N4.1 (G), sh1._232_.P4.1 (G)
sh1._046_: sh1._211_.N2.3 (D), sh1._211_.N4.3 (D), sh1._211_.P1.3 (D), sh1._211_.P2.3 (D), sh1._231_.N2.1 (G), sh1._231_.P2.1 (G), sh1._242_.N4.1 (G), sh1._242_.P4.1 (G)
sh1._047_: sh1._213_.N2.3 (D), sh1._213_.N4.3 (D), sh1._213_.P1.3 (D), sh1._213_.P2.3 (D), sh1._232_.N2.1 (G), sh1._232_.P2.1 (G), sh1._233_.N4.1 (G), sh1._233_.P4.1 (G)
sh1._048_: sh1._214_.N2.3 (D), sh1._214_.N4.3 (D), sh1._214_.P1.3 (D), sh1._214_.P2.3 (D), sh1._233_.N2.1 (G), sh1._233_.P2.1 (G), sh1._234_.N4.1 (G), sh1._234_.P4.1 (G)
sh1._049_: sh1._215_.N2.3 (D), sh1._215_.N4.3 (D), sh1._215_.P1.3 (D), sh1._215_.P2.3 (D), sh1._234_.N2.1 (G), sh1._234_.P2.1 (G), sh1._235_.N4.1 (G), sh1._235_.P4.1 (G)
sh1._050_: sh1._216_.N2.3 (D), sh1._216_.N4.3 (D), sh1._216_.P1.3 (D), sh1._216_.P2.3 (D), sh1._235_.N2.1 (G), sh1._235_.P2.1 (G), sh1._236_.N4.1 (G), sh1._236_.P4.1 (G)
sh1._051_: sh1._185_.N2.3 (D), sh1._185_.N4.3 (D), sh1._185_.P1.3 (D), sh1._185_.P2.3 (D), sh1._236_.N2.1 (G), sh1._236_.P2.1 (G), sh1._237_.N4.1 (G), sh1._237_.P4.1 (G)
sh1._052_: sh1._186_.N2.3 (D), sh1._186_.N4.3 (D), sh1._186_.P1.3 (D), sh1._186_.P2.3 (D), sh1._237_.N2.1 (G), sh1._237_.P2.1 (G), sh1._238_.N4.1 (G), sh1._238_.P4.1 (G)
sh1._053_: sh1._187_.N2.3 (D), sh1._187_.N4.3 (D), sh1._187_.P1.3 (D), sh1._187_.P2.3 (D), sh1._238_.N2.1 (G), sh1._238_.P2.1 (G), sh1._239_.N4.1 (G), sh1._239_.P4.1 (G)
sh1._054_: sh1._188_.N2.3 (D), sh1._188_.N4.3 (D), sh1._188_.P1.3 (D), sh1._188_.P2.3 (D), sh1._239_.N2.1 (G), sh1._239_.P2.1 (G), sh1._240_.N4.1 (G), sh1._240_.P4.1 (G)
sh1._055_: sh1._189_.N2.3 (D), sh1._189_.N4.3 (D), sh1._189_.P1.3 (D), sh1._189_.P2.3 (D), sh1._240_.N2.1 (G), sh1._240_.P2.1 (G), sh1._241_.N4.1 (G), sh1._241_.P4.1 (G)
sh1._056_: sh1._191_.N2.3 (D), sh1._191_.N4.3 (D), sh1._191_.P1.3 (D), sh1._191_.P2.3 (D), sh1._241_.N2.1 (G), sh1._241_.P2.1 (G), sh1._243_.N4.1 (G), sh1._243_.P4.1 (G)
sh1._057_: sh1._190_.N2.3 (D), sh1._190_.N4.3 (D), sh1._190_.P1.3 (D), sh1._190_.P2.3 (D), sh1._242_.N2.1 (G), sh1._242_.P2.1 (G), sh1._245_.N4.1 (G), sh1._245_.P4.1 (G)
sh1._058_: sh1._192_.N2.3 (D), sh1._192_.N4.3 (D), sh1._192_.P1.3 (D), sh1._192_.P2.3 (D), sh1._243_.N2.1 (G), sh1._243_.P2.1 (G), sh1._244_.N4.1 (G), sh1._244_.P4.1 (G)
sh1._059_: sh1._193_.N2.3 (D), sh1._193_.N4.3 (D), sh1._193_.P1.3 (D), sh1._193_.P2.3 (D), sh1._244_.N2.1 (G), sh1._244_.P2.1 (G)
sh1._060_: sh1._194_.N2.3 (D), sh1._194_.N4.3 (D), sh1._194_.P1.3 (D), sh1._194_.P2.3 (D), sh1._245_.N2.1 (G), sh1._245_.P2.1 (G), sh1._246_.N4.1 (G), sh1._246_.P4.1 (G)
sh1._061_: sh1._195_.N2.3 (D), sh1._195_.N4.3 (D), sh1._195_.P1.3 (D), sh1._195_.P2.3 (D), sh1._246_.N2.1 (G), sh1._246_.P2.1 (G), sh1._247_.N4.1 (G), sh1._247_.P4.1 (G)
sh1._062_: sh1._196_.N2.3 (D), sh1._196_.N4.3 (D), sh1._196_.P1.3 (D), sh1._196_.P2.3 (D), sh1._247_.N2.1 (G), sh1._247_.P2.1 (G), sh1._248_.N4.1 (G), sh1._248_.P4.1 (G)
sh1._063_: sh1._197_.N2.3 (D), sh1._197_.N4.3 (D), sh1._197_.P1.3 (D), sh1._197_.P2.3 (D), sh1._248_.N2.1 (G), sh1._248_.P2.1 (G), sh1._249_.N4.1 (G), sh1._249_.P4.1 (G)
sh1._064_: sh1._198_.N2.3 (D), sh1._198_.N4.3 (D), sh1._198_.P1.3 (D), sh1._198_.P2.3 (D), sh1._249_.N2.1 (G), sh1._249_.P2.1 (G), sh1._250_.N4.1 (G), sh1._250_.P4.1 (G)
sh1._065_: sh1._199_.N2.3 (D), sh1._199_.N4.3 (D), sh1._199_.P1.3 (D), sh1._199_.P2.3 (D), sh1._250_.N2.1 (G), sh1._250_.P2.1 (G), sh1._251_.N4.1 (G), sh1._251_.P4.1 (G)
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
